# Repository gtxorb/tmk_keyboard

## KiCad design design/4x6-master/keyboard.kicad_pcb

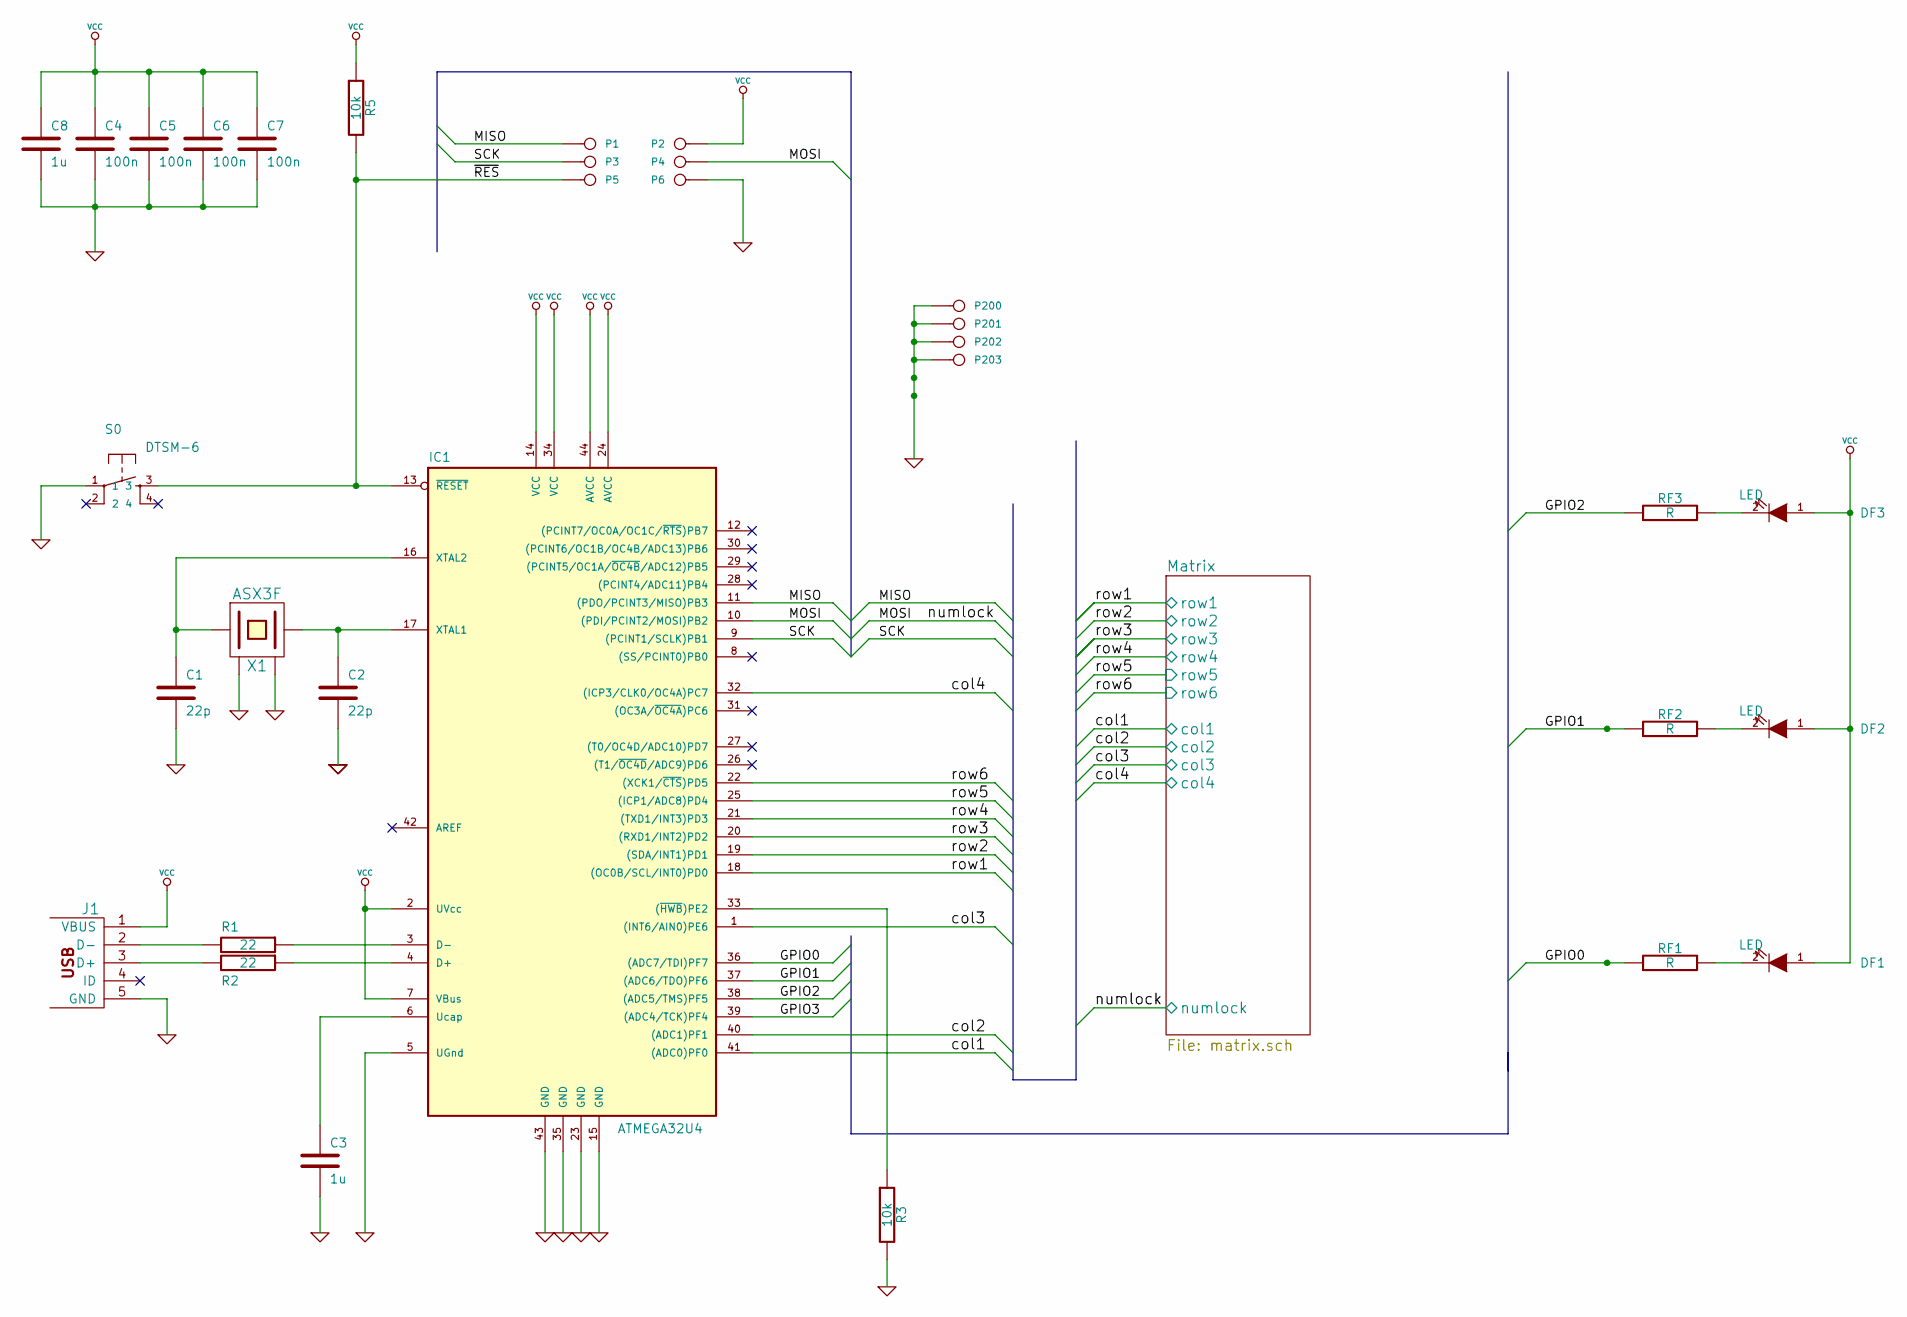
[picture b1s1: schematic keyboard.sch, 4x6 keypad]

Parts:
C1, C2: 22p
C3, C8: 1u
C4, C5, C6, C7: 100n
DF1, DF2, DF3: LED
IC1: ATMEGA32U4; TQFP44
J1: MINI
P1: MISO
P2: Vcc
P3: SCK
P4: MOSI
P5: RES
P6, P200, P201, P202, P203: GND
R1, R2: 22
R3, R5: 10k
RF1, RF2, RF3: R
S0: DTSM-6; switch-tact-DTSM-6
X1: ASX3F

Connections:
/GPIO0: IC1.36 ((ADC7/TDI)PF7), RF1.1
/GPIO1: IC1.37 ((ADC6/TDO)PF6), RF2.1
/GPIO2: IC1.38 ((ADC5/TMS)PF5), RF3.1
/MISO: IC1.11 ((PDO/PCINT3/MISO)PB3), P1.1
/Matrix/col1: IC1.41 ((ADC0)PF0); also elsewhere on the board
/Matrix/col2: IC1.40 ((ADC1)PF1); also elsewhere on the board
/Matrix/col3: IC1.1 ((INT6/AIN0)PE6); also elsewhere on the board
/Matrix/col4: IC1.32 ((ICP3/CLK0/OC4A)PC7); also elsewhere on the board
/Matrix/numlock: IC1.10 ((PDI/PCINT2/MOSI)PB2), P4.1; also elsewhere on the board
/Matrix/row1: IC1.18 ((OC0B/SCL/INT0)PD0); also elsewhere on the board
/Matrix/row2: IC1.19 ((SDA/INT1)PD1); also elsewhere on the board
/Matrix/row3: IC1.20 ((RXD1/INT2)PD2); also elsewhere on the board
/Matrix/row4: IC1.21 ((TXD1/INT3)PD3); also elsewhere on the board
/Matrix/row5: IC1.25 ((ICP1/ADC8)PD4); also elsewhere on the board
/Matrix/row6: IC1.22 ((XCK1/~CTS~)PD5); also elsewhere on the board
/SCK: IC1.9 ((PCINT1/SCLK)PB1), P3.1
/~RES~: IC1.13 (~RESET~), P5.1, R5.2, S0.3
GND: C1.2, C2.2, C3.2, C4.2, C5.2, C6.2, C7.2, C8.2, IC1.5 (UGnd), IC1.15 (GND), IC1.23 (GND), IC1.35 (GND), IC1.43 (GND), J1.5 (GND), P6.1, P200.1, P201.1, P202.1, P203.1, R3.2, S0.1, X1.2 (GND), X1.4 (GND)
unnamed: C1.1, IC1.16 (XTAL2), X1.1
unnamed: C2.1, IC1.17 (XTAL1), X1.3 (2)
unnamed: J1.2 (D-), R1.2
unnamed: J1.3 (D+), R2.2
unnamed: IC1.3 (D-), R1.1
unnamed: C3.1, IC1.6 (Ucap)
unnamed: IC1.4 (D+), R2.1
unnamed: IC1.33 ((~HWB~)PE2), R3.1
unnamed: DF3.2 (K), RF3.2
unnamed: DF1.2 (K), RF1.2
unnamed: DF2.2 (K), RF2.2
VCC: C4.1, C5.1, C6.1, C7.1, C8.1, DF1.1 (A), DF2.1 (A), DF3.1 (A), IC1.2 (UVcc), IC1.7 (VBus), IC1.14 (VCC), IC1.24 (AVCC), IC1.34 (VCC), IC1.44 (AVCC), J1.1 (VBUS), P2.1, R5.1; also elsewhere on the board

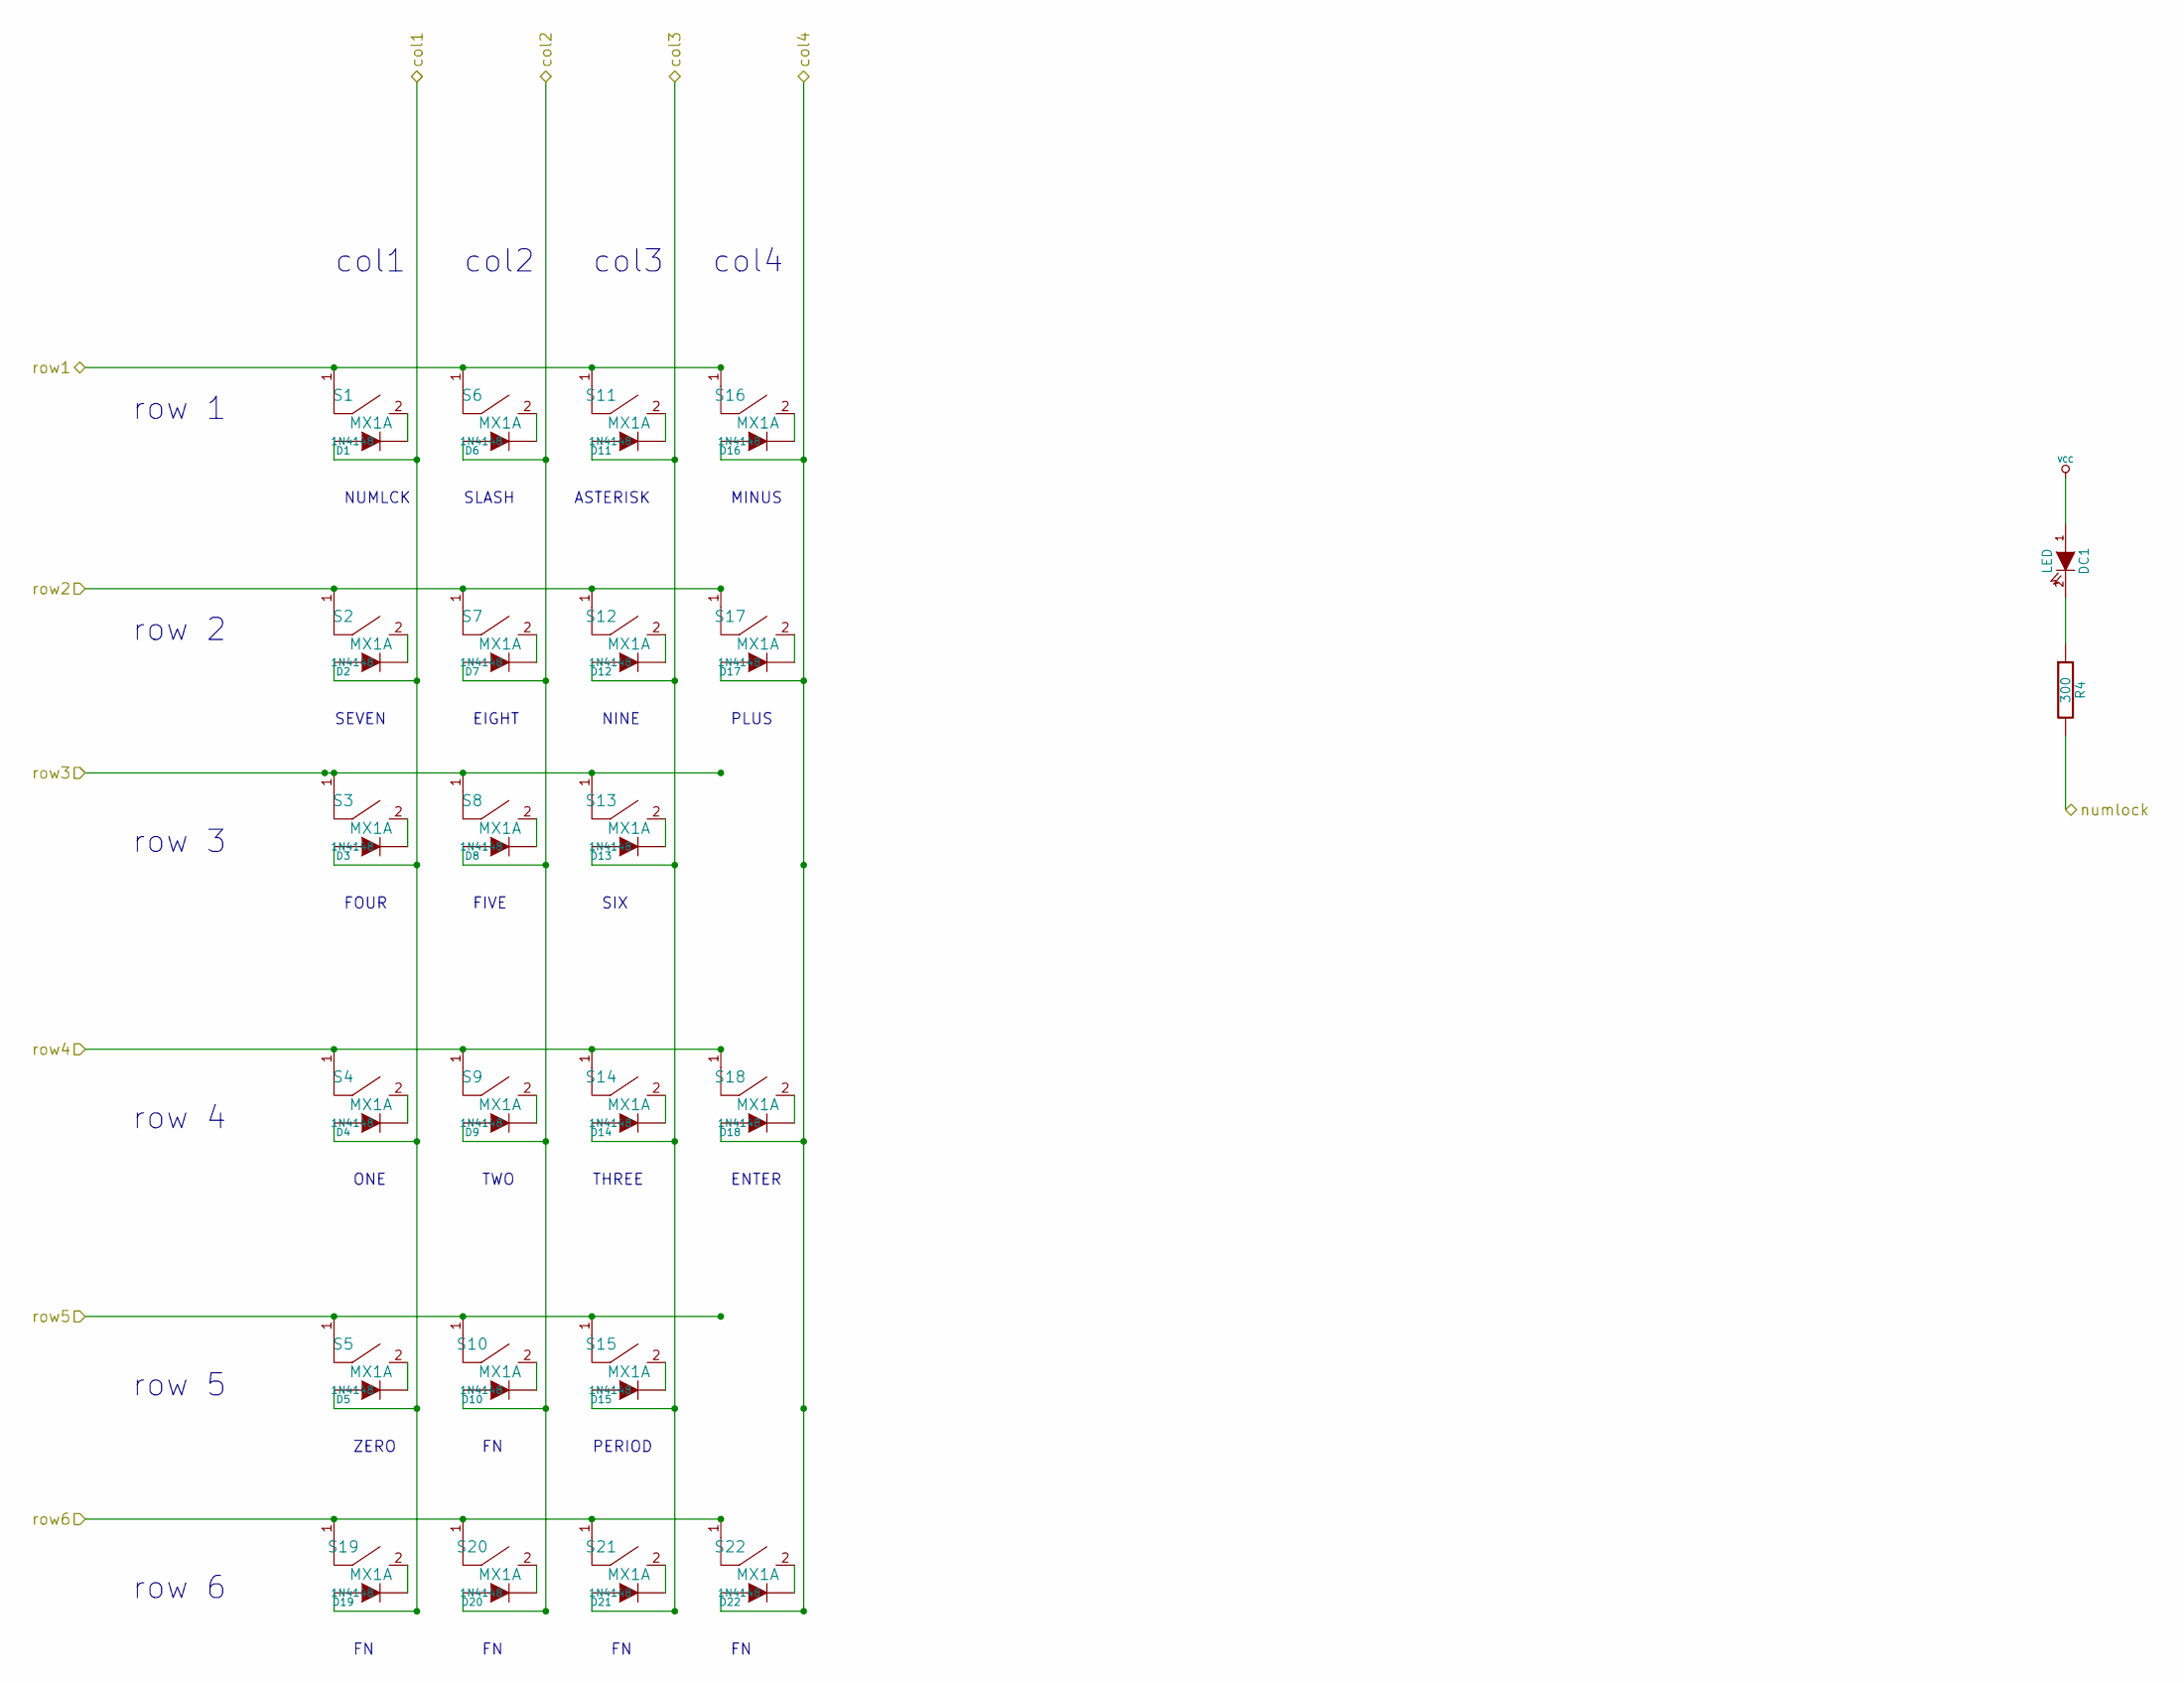
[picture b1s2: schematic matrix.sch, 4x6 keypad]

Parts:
D1, D2, D3, D4, D5, D6, D7, D8, D9, D10, D11, D12, D13, D14, D15, D16, D17, D18, D19, D20, D21, D22: 1N4148
DC1: LED
R4: 300
S1, S2, S3, S4, S5, S6, S7, S8, S9, S10, S11, S12, S13, S14, S15, S16, S17, S18, S19, S20, S21, S22: MX1A

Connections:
/Matrix/col1: D1.1 (A), D2.1 (A), D3.1 (A), D4.1 (A), D5.1 (A), D19.1 (A); also elsewhere on the board
/Matrix/col2: D6.1 (A), D7.1 (A), D8.1 (A), D9.1 (A), D10.1 (A), D20.1 (A); also elsewhere on the board
/Matrix/col3: D11.1 (A), D12.1 (A), D13.1 (A), D14.1 (A), D15.1 (A), D21.1 (A); also elsewhere on the board
/Matrix/col4: D16.1 (A), D17.1 (A), D18.1 (A), D22.1 (A); also elsewhere on the board
/Matrix/numlock: R4.2; also elsewhere on the board
/Matrix/row1: S1.1, S6.1, S11.1, S16.1; also elsewhere on the board
/Matrix/row2: S2.1, S7.1, S12.1, S17.1; also elsewhere on the board
/Matrix/row3: S3.1, S8.1, S13.1; also elsewhere on the board
/Matrix/row4: S4.1, S9.1, S14.1, S18.1; also elsewhere on the board
/Matrix/row5: S5.1, S10.1, S15.1; also elsewhere on the board
/Matrix/row6: S19.1, S20.1, S21.1, S22.1; also elsewhere on the board
unnamed: D4.2 (K), S4.2
unnamed: D18.2 (K), S18.2
unnamed: D3.2 (K), S3.2
unnamed: D5.2 (K), S5.2
unnamed: D10.2 (K), S10.2
unnamed: D15.2 (K), S15.2
unnamed: D16.2 (K), S16.2
unnamed: D17.2 (K), S17.2
unnamed: D1.2 (K), S1.2
unnamed: D20.2 (K), S20.2
unnamed: D21.2 (K), S21.2
unnamed: D19.2 (K), S19.2
unnamed: D22.2 (K), S22.2
unnamed: DC1.2 (K), R4.1
unnamed: D6.2 (K), S6.2
unnamed: D11.2 (K), S11.2
unnamed: D2.2 (K), S2.2
unnamed: D7.2 (K), S7.2
unnamed: D12.2 (K), S12.2
unnamed: D8.2 (K), S8.2
unnamed: D13.2 (K), S13.2
unnamed: D9.2 (K), S9.2
unnamed: D14.2 (K), S14.2
VCC: DC1.1 (A); also elsewhere on the board

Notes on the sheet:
row 1
row 2
row 3
row 4
col1
col2
col3
col4
NUMLCK
SEVEN
SLASH
ASTERISK
MINUS
FOUR
EIGHT
NINE
PLUS
ONE
TWO
THREE
FIVE
SIX
ENTER
row 5
ZERO
PERIOD
row 6

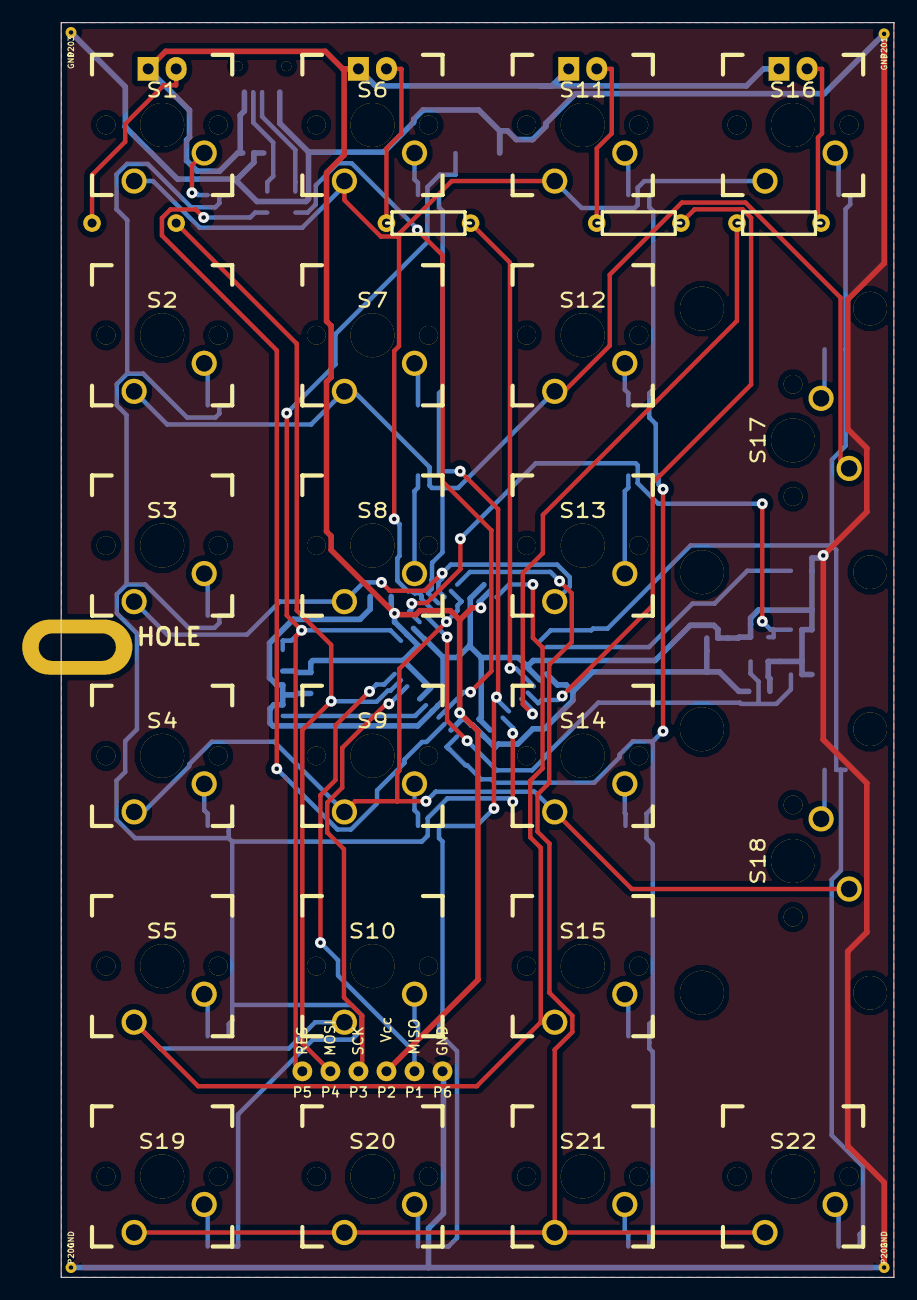
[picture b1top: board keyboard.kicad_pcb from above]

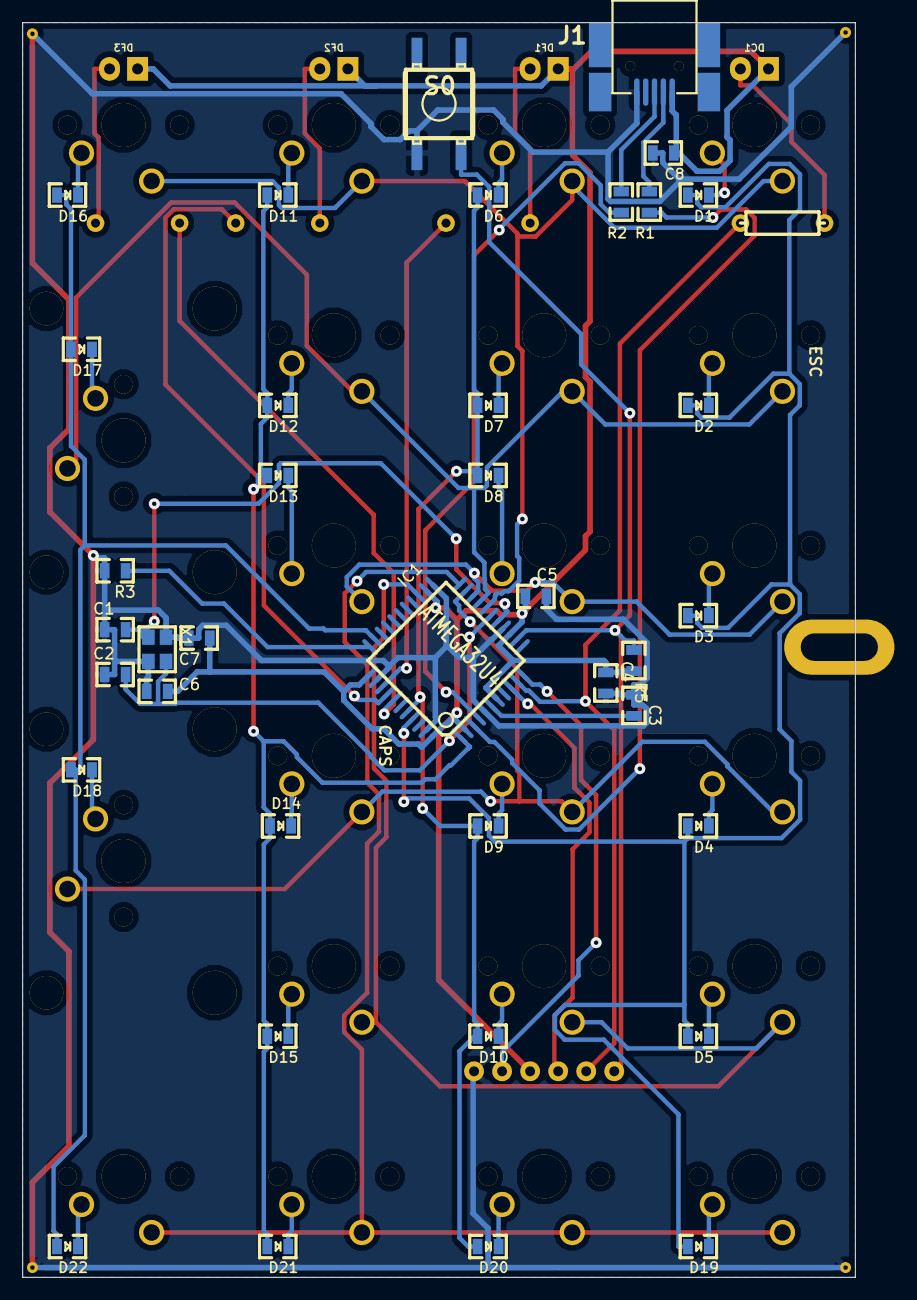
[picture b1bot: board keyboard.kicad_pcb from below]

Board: 2 copper layers, 75.4 x 113.7 mm, 79 parts (39 on the bottom side), 53 nets.

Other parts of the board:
H2: HOLE; PKRHSL

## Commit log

2016-08-11 fist upload
2016-08-19 wireless_split
